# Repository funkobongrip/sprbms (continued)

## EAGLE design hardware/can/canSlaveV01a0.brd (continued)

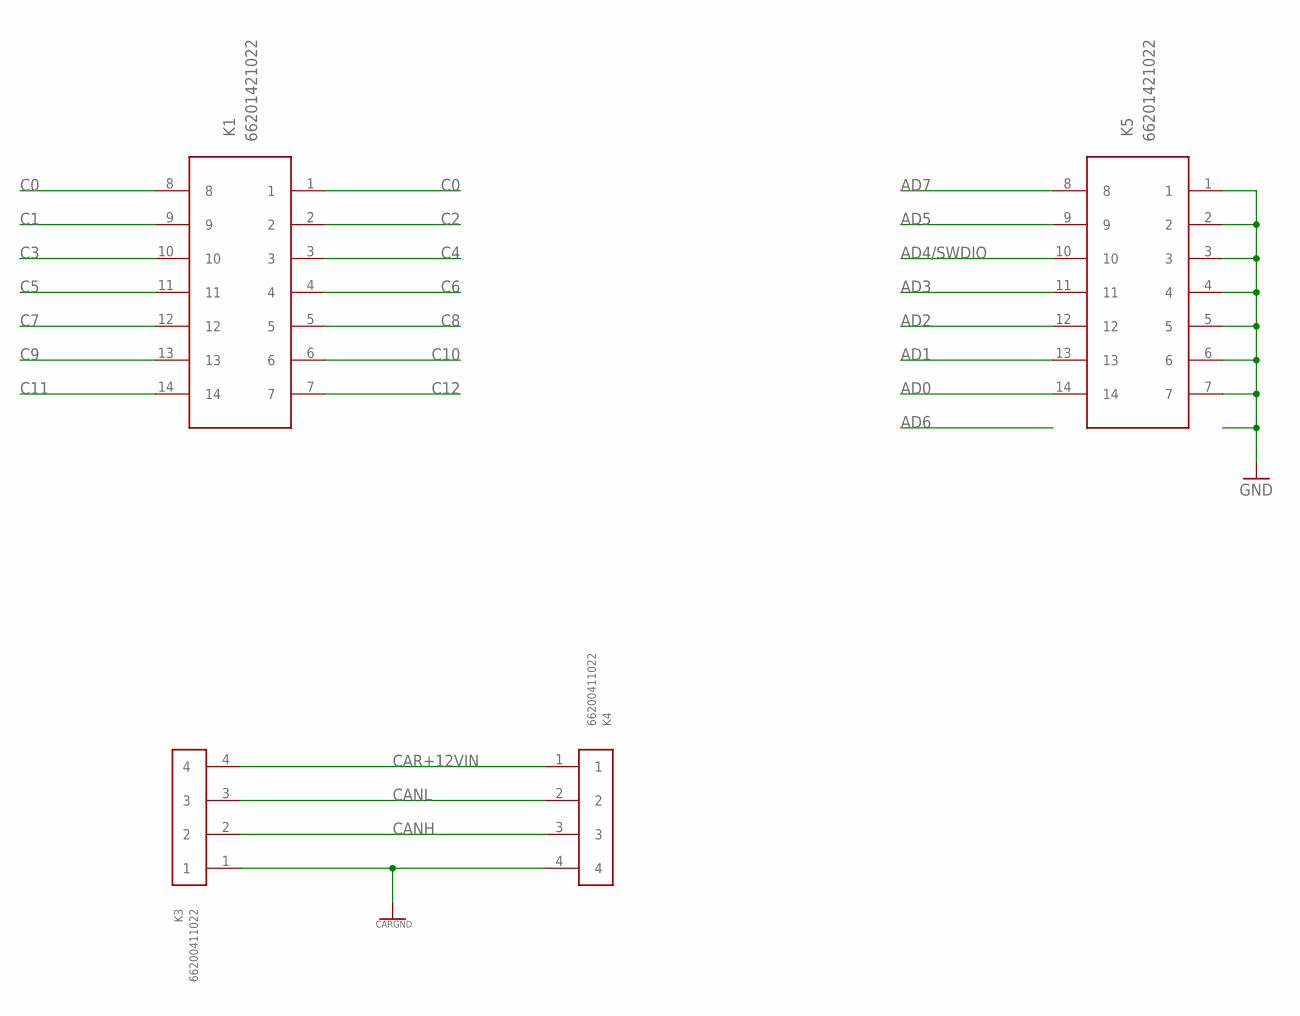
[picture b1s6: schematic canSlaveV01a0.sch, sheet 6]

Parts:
K1, K5: 66201421022
K3, K4: 66200411022

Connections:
AD0: K5.14; also elsewhere on the board
AD1: K5.13; also elsewhere on the board
AD2: K5.12; also elsewhere on the board
AD3: K5.11; also elsewhere on the board
AD4/SWDIO: K5.10; also elsewhere on the board
AD5: K5.9; also elsewhere on the board
AD7: K5.8; also elsewhere on the board
C0: K1.1, K1.8; also elsewhere on the board
C1: K1.9; also elsewhere on the board
C2: K1.2; also elsewhere on the board
C3: K1.10; also elsewhere on the board
C4: K1.3; also elsewhere on the board
C5: K1.11; also elsewhere on the board
C6: K1.4; also elsewhere on the board
C7: K1.12; also elsewhere on the board
C8: K1.5; also elsewhere on the board
C9: K1.13; also elsewhere on the board
C10: K1.6; also elsewhere on the board
C11: K1.14; also elsewhere on the board
C12: K1.7; also elsewhere on the board
CANH: K3.2, K4.3; also elsewhere on the board
CANL: K3.3, K4.2; also elsewhere on the board
CAR+12VIN: K3.4, K4.1; also elsewhere on the board
CARGND: K3.1, K4.4; also elsewhere on the board
GND: K5.1, K5.2, K5.3, K5.4, K5.5, K5.6, K5.7; also elsewhere on the board

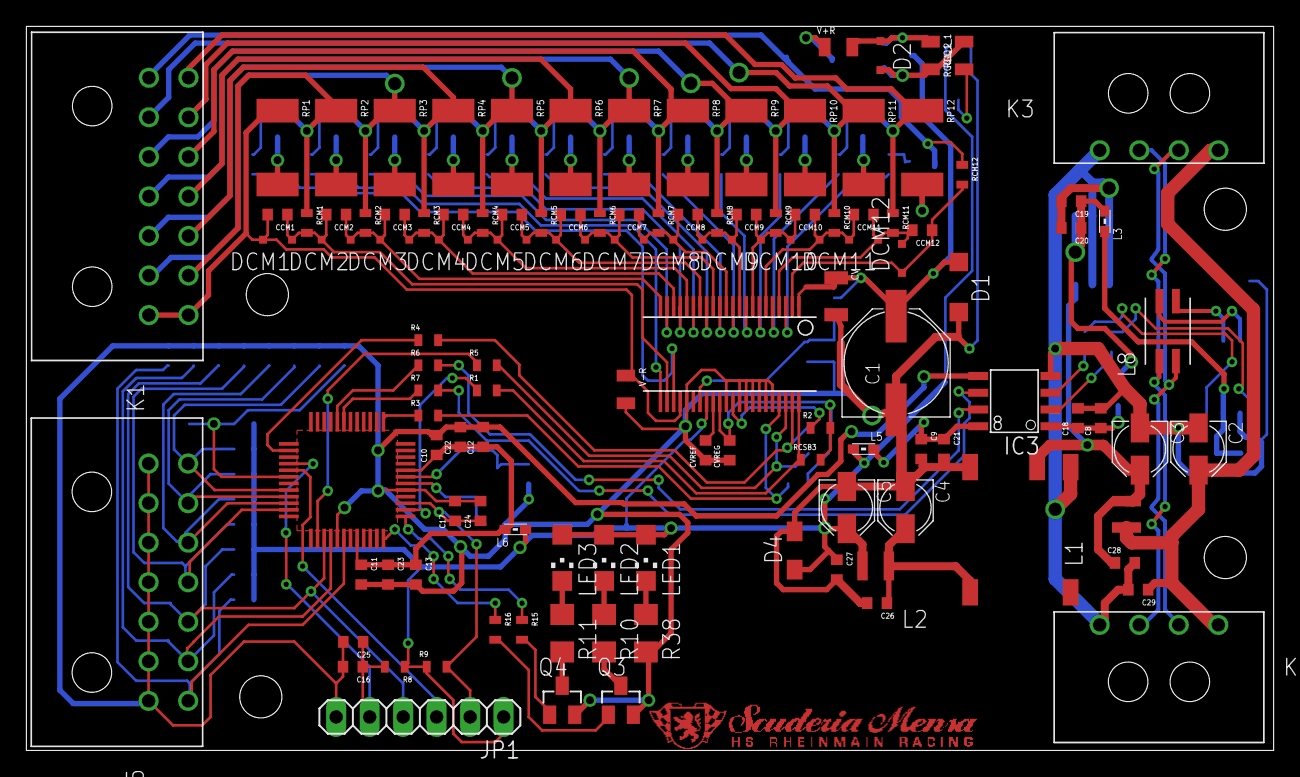
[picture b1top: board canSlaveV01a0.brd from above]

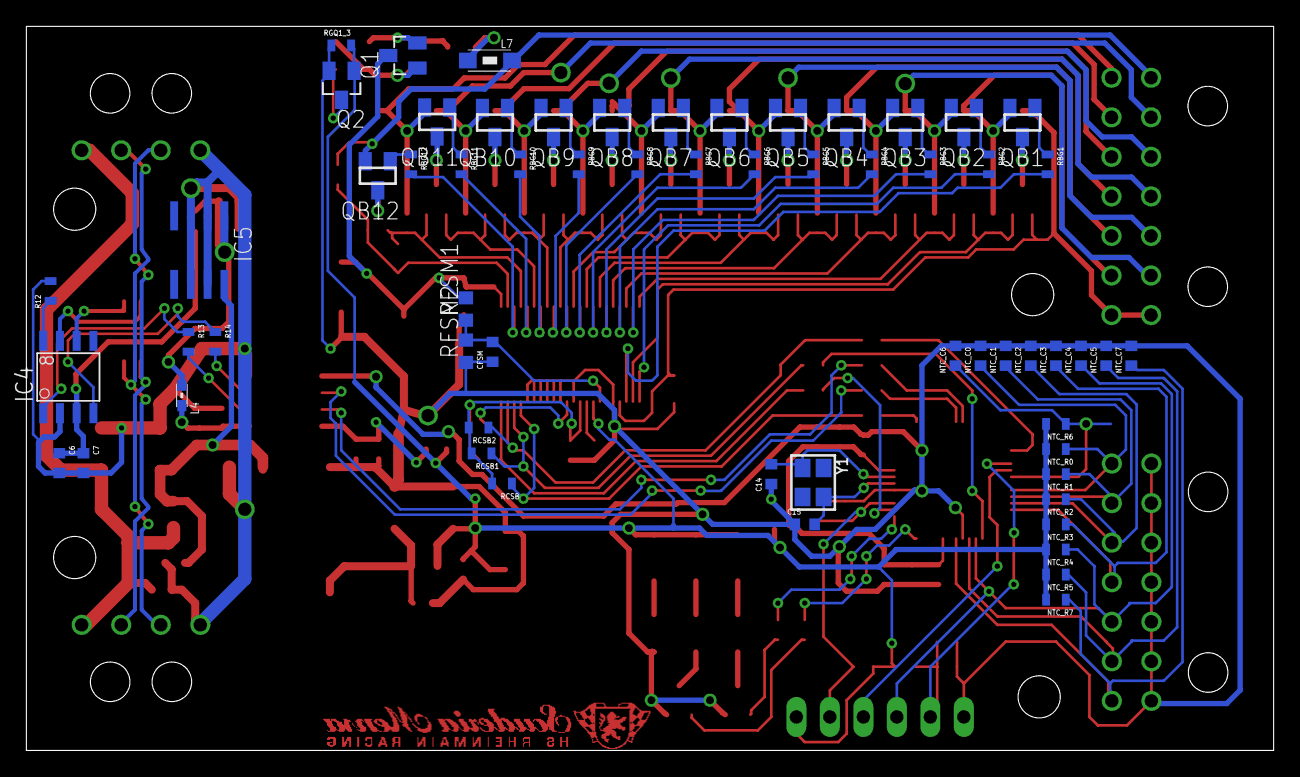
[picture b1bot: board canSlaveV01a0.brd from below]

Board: 2 copper layers, 94.6 x 54.9 mm, 180 parts (61 on the bottom side), 124 nets.

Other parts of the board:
U$15: SMLOGOS
